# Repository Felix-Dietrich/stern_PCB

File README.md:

Housing for four 21700 cells and PCB is on onshape: https://cad.onshape.com/documents/7a57a716b7607c04f3957bb7/w/b1331918a3535d202a224eb3/e/a3f7e8ff6c7ca0a37da96c1e?renderMode=0&uiState=67293fd1cffb950f3f58066c

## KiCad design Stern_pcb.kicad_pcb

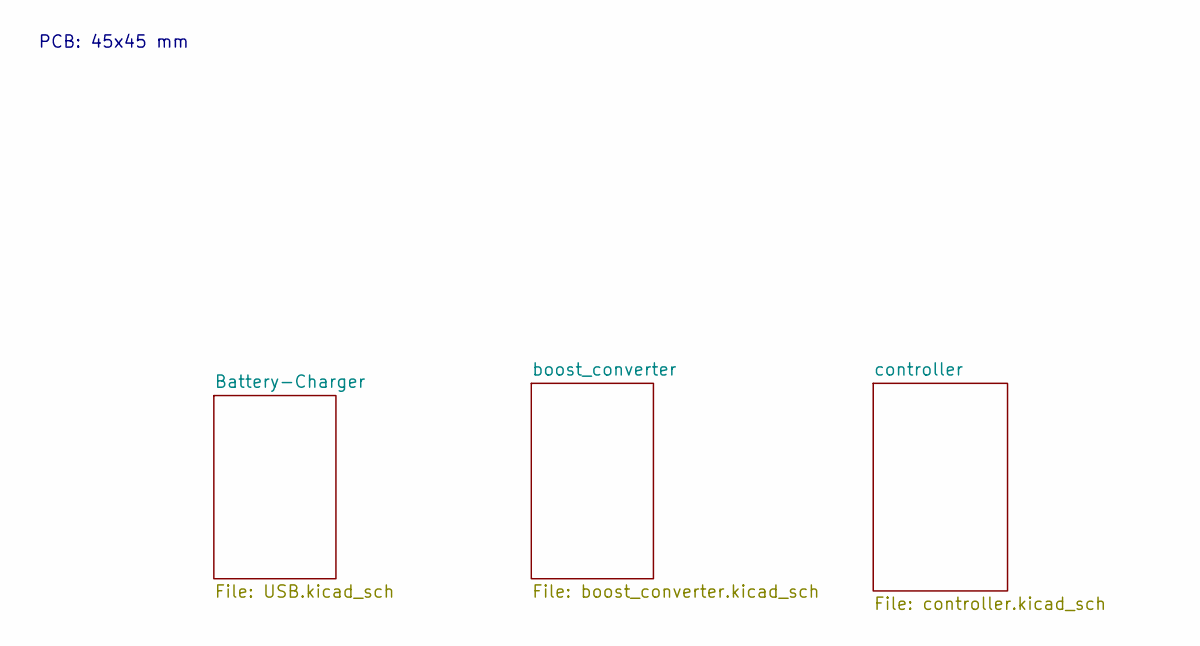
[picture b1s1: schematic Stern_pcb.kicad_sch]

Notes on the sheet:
PCB: 45x45 mm

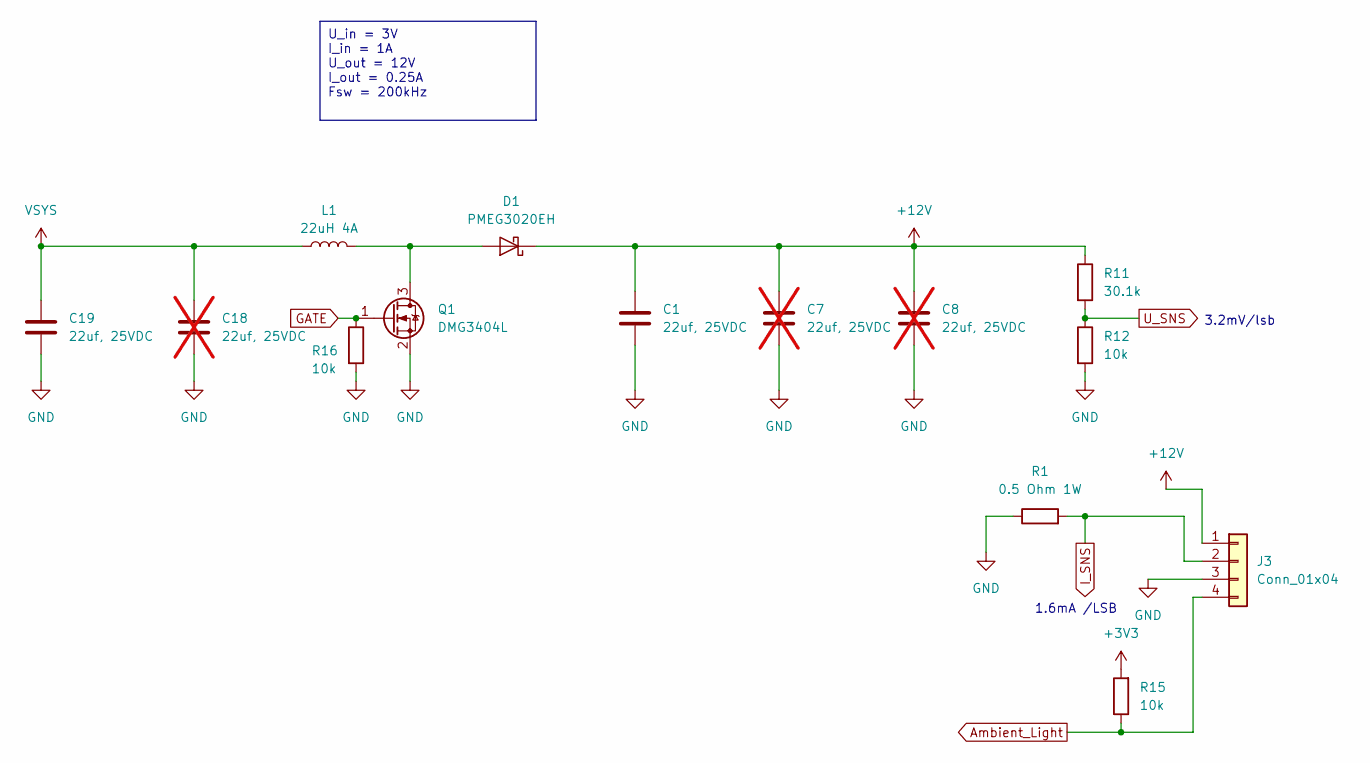
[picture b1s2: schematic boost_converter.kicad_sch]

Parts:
C1, C19: 22uf, 25VDC; C_0805_2012Metric_Pad1.18x1.45mm_HandSolder; MPN CL21A226MAYNNNE
C7, C8, C18: 22uf, 25VDC; C_0805_2012Metric_Pad1.18x1.45mm_HandSolder; MPN CL21A226MAYNNNE; not fitted
D1: PMEG3020EH; D_SOD-123F
J3: Conn_01x04; PinHeader_1x04_P2.54mm_Vertical
L1: 22uH 4A; L_Bourns_SRR1260_handsolder; MPN SRR1260-220M
Q1: DMG3404L; SOT-23
R1: 0.5 Ohm 1W; R_1206_3216Metric_Pad1.30x1.75mm_HandSolder; MPN MFHA1206R5000FC
R11: 30.1k; R_0603_1608Metric_Pad0.98x0.95mm_HandSolder
R12, R15, R16: 10k; R_0603_1608Metric_Pad0.98x0.95mm_HandSolder

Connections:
+3V3: R15.2; also elsewhere on the board
+12V: C1.1, C7.1, C8.1, D1.1 (K), J3.1, R11.1
Ambient_Light: J3.4, R15.1; also elsewhere on the board
GATE: Q1.1 (G), R16.1; also elsewhere on the board
GND: C1.2, C7.2, C8.2, C18.2, C19.2, J3.3, Q1.2 (S), R1.1, R12.2, R16.2; also elsewhere on the board
I_SNS: J3.2, R1.2; also elsewhere on the board
unnamed: D1.2 (A), L1.2, Q1.3 (D)
U_SNS: R11.2, R12.1; also elsewhere on the board
VSYS: C18.1, C19.1, L1.1; also elsewhere on the board

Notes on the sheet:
U_in = 3V I_in = 1A U_out = 12V I_out = 0.25A Fsw = 200kHz
3.2mV/lsb
1.6mA /LSB

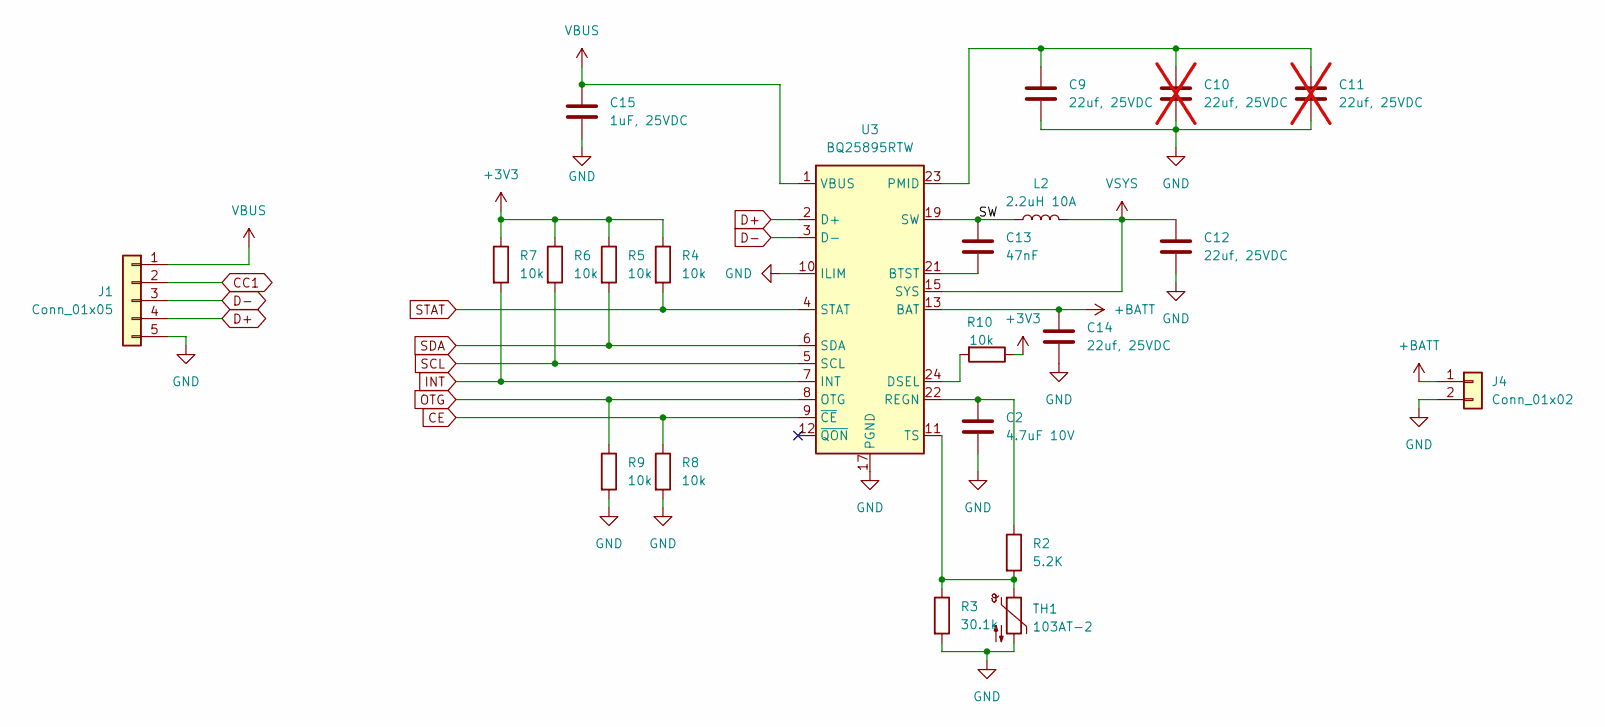
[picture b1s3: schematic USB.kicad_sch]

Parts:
C2: 4.7uF 10V; C_0603_1608Metric_Pad1.08x0.95mm_HandSolder
C9, C12, C14: 22uf, 25VDC; C_0805_2012Metric_Pad1.18x1.45mm_HandSolder; MPN CL21A226MAYNNNE
C10, C11: 22uf, 25VDC; C_0805_2012Metric_Pad1.18x1.45mm_HandSolder; MPN CL21A226MAYNNNE; not fitted
C13: 47nF; C_0603_1608Metric_Pad1.08x0.95mm_HandSolder
C15: 1uF, 25VDC; C_0603_1608Metric_Pad1.08x0.95mm_HandSolder
J1: Conn_01x05; JST_PH_B5B-PH-K_1x05_P2.00mm_Vertical
J4: Conn_01x02; JST_EH_B2B-EH-A_1x02_P2.50mm_Vertical
L2: 2.2uH 10A; L_PSA_WLPMA0A040; MPN WLPMA0A040M2R2LC
R2: 5.2K; R_0603_1608Metric_Pad0.98x0.95mm_HandSolder
R3: 30.1k; R_0603_1608Metric_Pad0.98x0.95mm_HandSolder
R4, R5, R6, R7, R8, R9, R10: 10k; R_0603_1608Metric_Pad0.98x0.95mm_HandSolder
TH1: 103AT-2; PinHeader_1x02_P2.54mm_Vertical; MPN 103AT-2
U3: BQ25895RTW; Texas_RTW_WQFN-24-1EP_4x4mm_P0.5mm_EP2.7x2.7mm_ThermalVias

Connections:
+3V3: R4.1, R5.1, R6.1, R7.1, R10.1; also elsewhere on the board
+BATT: C14.1, J4.1, U3.13 (BAT), U3.14 (BAT)
/Battery-Charger/SW: C13.1, L2.1, U3.19 (SW), U3.20 (SW)
CC1: J1.2; also elsewhere on the board
CE: R8.1, U3.9 (~CE); also elsewhere on the board
D+: J1.4, U3.2 (D+)
D-: J1.3, U3.3 (D-)
GND: C2.2, C9.2, C10.2, C11.2, C12.2, C14.2, C15.2, J1.5, J4.2, R3.2, R8.2, R9.2, TH1.2, U3.10 (ILIM), U3.17 (PGND), U3.18 (PGND), U3.25 (PGND); also elsewhere on the board
INT: R7.2, U3.7 (INT); also elsewhere on the board
unnamed: C13.2, U3.21 (BTST)
unnamed: R10.2, U3.24 (DSEL)
unnamed: C9.1, C10.1, C11.1, U3.23 (PMID)
unnamed: C2.1, R2.1, U3.22 (REGN)
unnamed: R2.2, R3.1, TH1.1, U3.11 (TS)
OTG: R9.1, U3.8 (OTG); also elsewhere on the board
SCL: R6.2, U3.5 (SCL); also elsewhere on the board
SDA: R5.2, U3.6 (SDA); also elsewhere on the board
STAT: R4.2, U3.4 (STAT); also elsewhere on the board
VBUS: C15.1, J1.1, U3.1 (VBUS)
VSYS: C12.1, L2.2, U3.15 (SYS), U3.16 (SYS); also elsewhere on the board

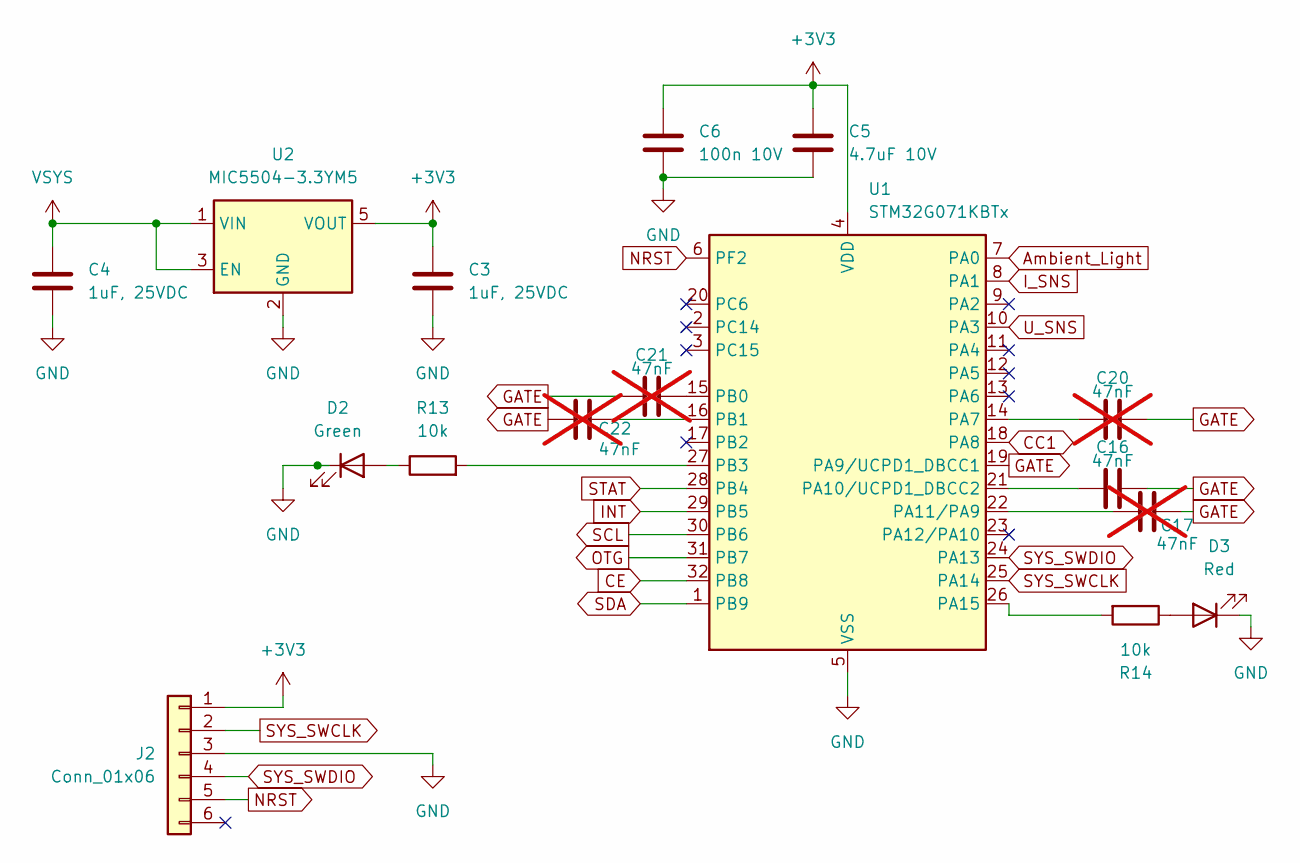
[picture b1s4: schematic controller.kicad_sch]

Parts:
C3, C4: 1uF, 25VDC; C_0603_1608Metric_Pad1.08x0.95mm_HandSolder
C5: 4.7uF 10V; C_0603_1608Metric_Pad1.08x0.95mm_HandSolder
C6: 100n 10V; C_0603_1608Metric_Pad1.08x0.95mm_HandSolder
C16: 47nF; C_0603_1608Metric_Pad1.08x0.95mm_HandSolder
C17, C20, C21, C22: 47nF; C_0603_1608Metric_Pad1.08x0.95mm_HandSolder; not fitted
D2: Green; LED_0805_2012Metric_Pad1.15x1.40mm_HandSolder; MPN 150080GS75000
D3: Red; LED_0805_2012Metric_Pad1.15x1.40mm_HandSolder; MPN 150080RS75000
J2: Conn_01x06; PinHeader_1x06_P2.54mm_Vertical
R13, R14: 10k; R_0603_1608Metric_Pad0.98x0.95mm_HandSolder
U1: STM32G071KBTx; LQFP-32_7x7mm_P0.8mm
U2: MIC5504-3.3YM5; SOT-23-5

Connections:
+3V3: C3.1, C5.1, C6.1, J2.1, U1.4 (VDD), U2.5 (VOUT); also elsewhere on the board
Ambient_Light: U1.7 (PA0); also elsewhere on the board
CC1: U1.18 (PA8); also elsewhere on the board
CE: U1.32 (PB8); also elsewhere on the board
GATE: C16.2, C17.2, C20.2, C21.1, C22.1, U1.19 (PA9/UCPD1_DBCC1); also elsewhere on the board
GND: C3.2, C4.2, C5.2, C6.2, D2.1 (K), D3.1 (K), J2.3, U1.5 (VSS), U2.2 (GND); also elsewhere on the board
INT: U1.29 (PB5); also elsewhere on the board
I_SNS: U1.8 (PA1); also elsewhere on the board
NRST: J2.5, U1.6 (PF2)
unnamed: D2.2 (A), R13.1
unnamed: D3.2 (A), R14.1
unnamed: C20.1, U1.14 (PA7)
unnamed: C16.1, U1.21 (PA10/UCPD1_DBCC2)
unnamed: C17.1, U1.22 (PA11/PA9)
unnamed: R14.2, U1.26 (PA15)
unnamed: C21.2, U1.15 (PB0)
unnamed: C22.2, U1.16 (PB1)
unnamed: R13.2, U1.27 (PB3)
OTG: U1.31 (PB7); also elsewhere on the board
SCL: U1.30 (PB6); also elsewhere on the board
SDA: U1.1 (PB9); also elsewhere on the board
STAT: U1.28 (PB4); also elsewhere on the board
SYS_SWCLK: J2.2, U1.25 (PA14)
SYS_SWDIO: J2.4, U1.24 (PA13)
U_SNS: U1.10 (PA3); also elsewhere on the board
VSYS: C4.1, U2.1 (VIN), U2.3 (EN); also elsewhere on the board

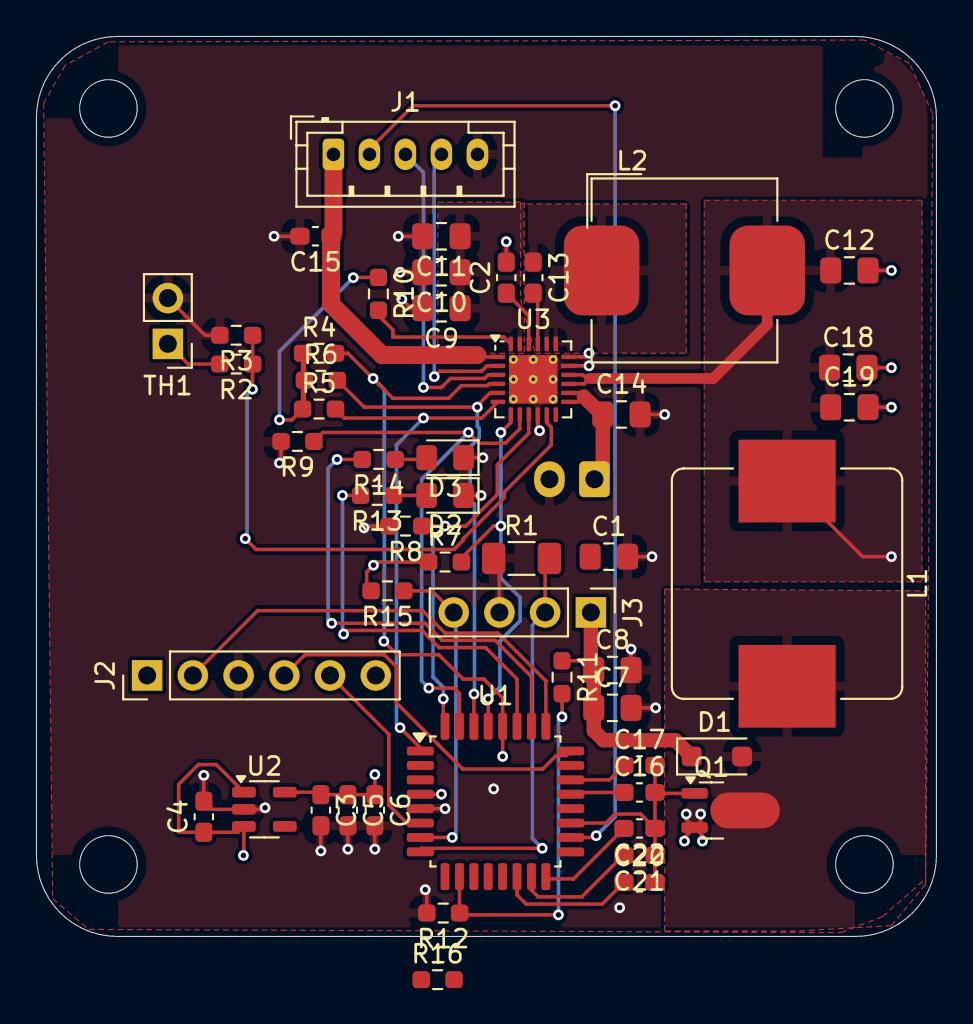
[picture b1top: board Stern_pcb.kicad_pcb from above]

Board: 4 copper layers, 50.0 x 50.0 mm, 52 parts (1 on the bottom side), 38 nets.

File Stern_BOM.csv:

"Reference","Value","Footprint","Qty","DNP","MPN","Manufacturer"
"C1,C9,C12,C14,C19","22uf, 25VDC","Capacitor_SMD:C_0805_2012Metric_Pad1.18x1.45mm_HandSolder","5","","CL21A226MAYNNNE",""
"C2,C5","4.7uF 10V","Capacitor_SMD:C_0603_1608Metric_Pad1.08x0.95mm_HandSolder","2","","",""
"C3,C4,C15","1uF, 25VDC","Capacitor_SMD:C_0603_1608Metric_Pad1.08x0.95mm_HandSolder","3","","",""
"C6","100n 10V","Capacitor_SMD:C_0603_1608Metric_Pad1.08x0.95mm_HandSolder","1","","",""
"C7,C8,C10,C11,C18","22uf, 25VDC","Capacitor_SMD:C_0805_2012Metric_Pad1.18x1.45mm_HandSolder","5","DNP","CL21A226MAYNNNE",""
"C13,C16,C17,C20,C21,C22","47nF","Capacitor_SMD:C_0603_1608Metric_Pad1.08x0.95mm_HandSolder","6","","",""
"D1","PMEG3020EH","Diode_SMD:D_SOD-123F","1","","",""
"D2","Green","LED_SMD:LED_0805_2012Metric_Pad1.15x1.40mm_HandSolder","1","","150080GS75000","Wurth"
"D3","Red","LED_SMD:LED_0805_2012Metric_Pad1.15x1.40mm_HandSolder","1","","150080RS75000","Wurth"
"J1","Conn_01x05","Connector_JST:JST_PH_B5B-PH-K_1x05_P2.00mm_Vertical","1","","",""
"J2","Conn_01x06","Connector_PinHeader_2.54mm:PinHeader_1x06_P2.54mm_Vertical","1","","",""
"J3","Conn_01x04","Connector_PinHeader_2.54mm:PinHeader_1x04_P2.54mm_Vertical","1","","",""
"J4","Conn_01x02","Connector_JST:JST_EH_B2B-EH-A_1x02_P2.50mm_Vertical","1","","",""
"L1","22uH 4A","Inductor_SMD:L_Bourns_SRR1260_handsolder","1","","SRR1260-220M","Bourns"
"L2","2.2uH 10A","Inductor_SMD:L_PSA_WLPMA0A040","1","","WLPMA0A040M2R2LC","WALSIN"
"Q1","DMG3404L","Package_TO_SOT_SMD:SOT-23","1","","",""
"R1","0.5 Ohm 1W","Resistor_SMD:R_1206_3216Metric_Pad1.30x1.75mm_HandSolder","1","","MFHA1206R5000FC","EATON"
"R2","5.2K","Resistor_SMD:R_0603_1608Metric_Pad0.98x0.95mm_HandSolder","1","","",""
"R3,R11","30.1k","Resistor_SMD:R_0603_1608Metric_Pad0.98x0.95mm_HandSolder","2","","",""
"R4,R5,R6,R7,R8,R9,R10,R12,R13,R14,R15","10k","Resistor_SMD:R_0603_1608Metric_Pad0.98x0.95mm_HandSolder","11","","",""
"TH1","103AT-2","Connector_PinHeader_2.54mm:PinHeader_1x02_P2.54mm_Vertical","1","","103AT-2","Semitec"
"U1","STM32G071KBTx","Package_QFP:LQFP-32_7x7mm_P0.8mm","1","","",""
"U2","MIC5504-3.3YM5","Package_TO_SOT_SMD:SOT-23-5","1","","",""
"U3","BQ25895RTW","Package_DFN_QFN:Texas_RTW_WQFN-24-1EP_4x4mm_P0.5mm_EP2.7x2.7mm_ThermalVias","1","","",""

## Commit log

2024-09-22 add gitignore
2024-09-22 improved gitignore
2024-09-22 igmore.lck
2024-09-22 created kicad project
2024-10-06 Updated USB-charger Schematics
2024-10-09 assigned footprints
2024-10-13 Layout begonnen
2024-10-30 marked unused capaacitors as not placed. Pull down on gate channel
2024-11-01 Verbindung zum Temperatursensor war falsch
